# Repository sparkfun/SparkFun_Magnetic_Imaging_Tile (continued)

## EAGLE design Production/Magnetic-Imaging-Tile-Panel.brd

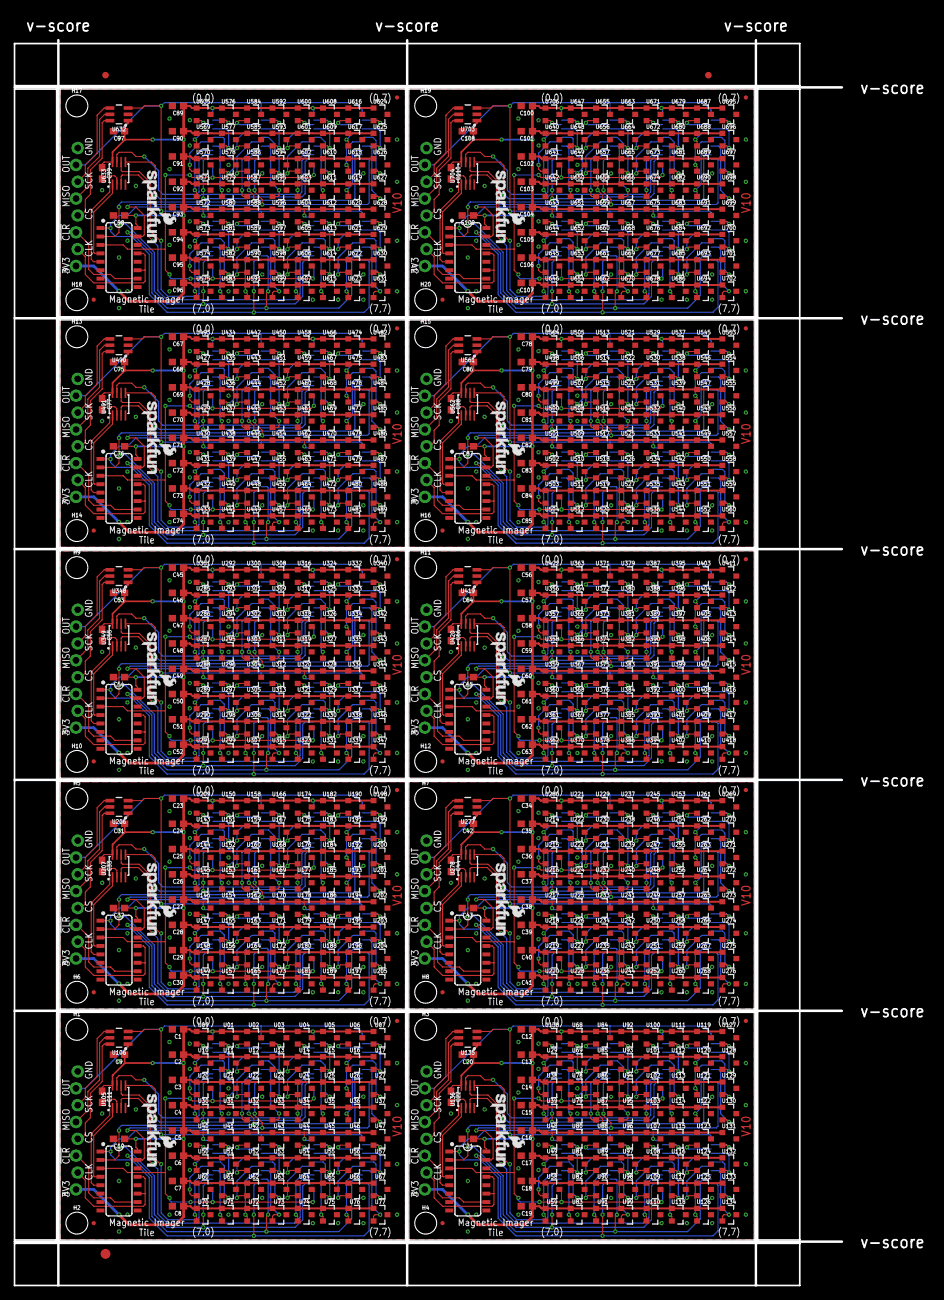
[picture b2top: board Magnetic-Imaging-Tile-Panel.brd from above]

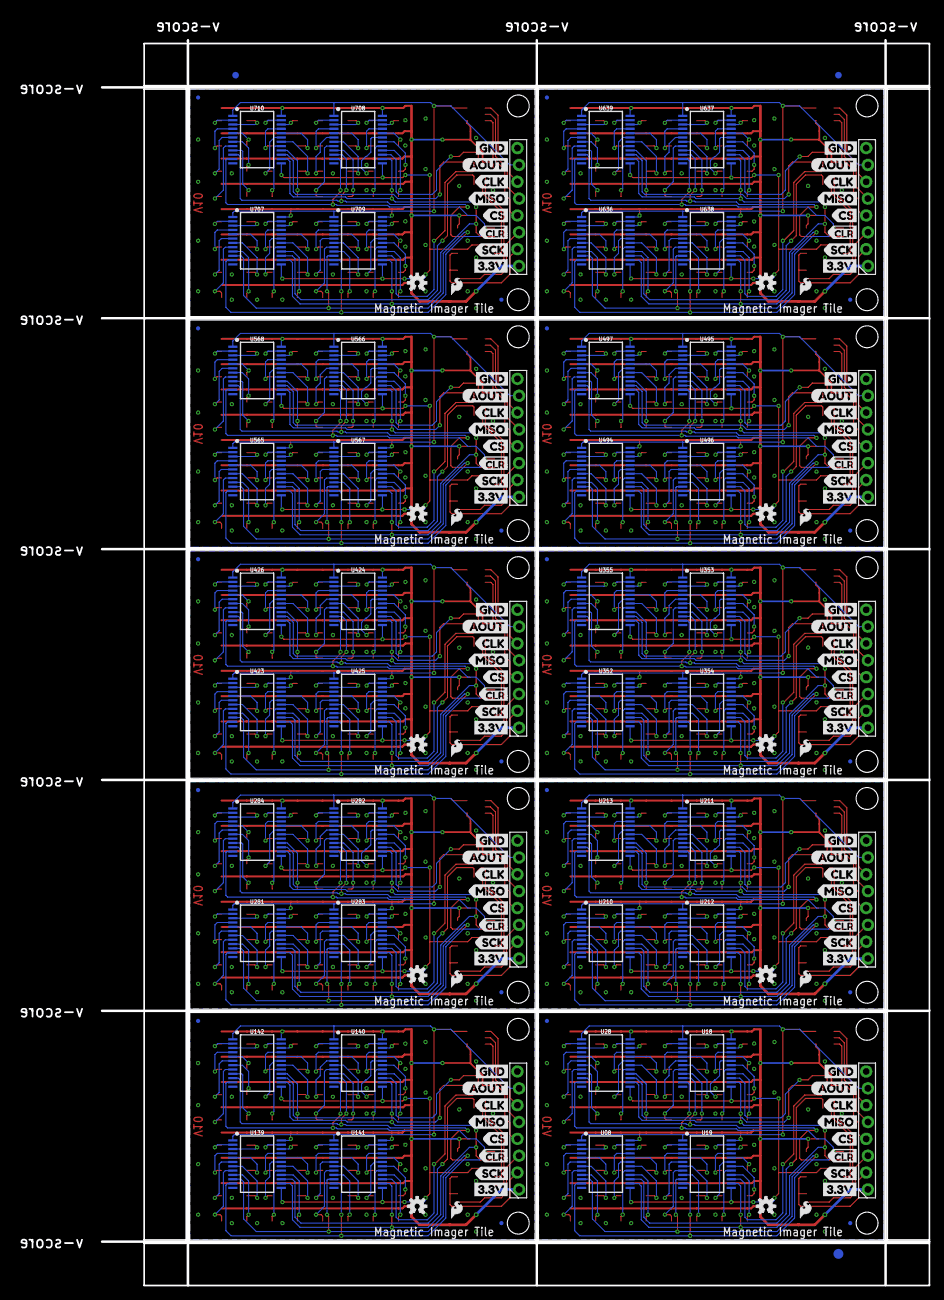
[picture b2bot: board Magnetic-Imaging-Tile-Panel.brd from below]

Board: 2 copper layers, 124.7 x 187.7 mm, 1016 parts (163 on the bottom side), 820 nets.

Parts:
C1, C2, C3, C4, C5, C6, C7, C8, C12, C13, C14, C15, C16, C17, C18, C19, C23, C24, C25, C26, C27, C28, C29, C30, C34, C35, C36, C37, C38, C39, C40, C41, C45, C46, C47, C48, C49, C50, C51, C52, C56, C57, C58, C59, C60, C61, C62, C63, C67, C68, C69, C70, C71, C72, C73, C74, C78, C79, C80, C81, C82, C83, C84, C85, C89, C90, C91, C92, C93, C94, C95, C96, C100, C101, C102, C103, C104, C105, C106, C107: 4.7uF; 0603
C9, C10, C11, C20, C21, C22, C31, C32, C33, C42, C43, C44, C53, C54, C55, C64, C65, C66, C75, C76, C77, C86, C87, C88, C97, C98, C99, C108, C109, C110: 0.1uF; 0603
E$1, E$2, E$3, E$4: FIDUCIAL-1X2
E$5, E$6: FIDUCIAL-1.5X3
FD1, FD2, FD3, FD4, FD5, FD6, FD7, FD8, FD9, FD10, FD11, FD12, FD13, FD14, FD15, FD16, FD17, FD18, FD19, FD20, FD21, FD22, FD23, FD24, FD25, FD26, FD27, FD28, FD29, FD30, FD31, FD32, FD33, FD34, FD35, FD36, FD37, FD38, FD39, FD40: FIDUCIALUFIDUCIAL; FIDUCIAL-MICRO
H1, H2, H3, H4, H5, H6, H7, H8, H9, H10, H11, H12, H13, H14, H15, H16, H17, H18, H19, H20: STAND-OFF
J1, J2, J3, J4, J5, J6, J7, J8, J9, J10: 1X08_LOCK_NO_SILK
LOGO1, LOGO3, LOGO5, LOGO7, LOGO9, LOGO11, LOGO13, LOGO15, LOGO17, LOGO19: SFE_LOGO_NAME.1_INCH; SFE_LOGO_NAME_.1
LOGO2, LOGO4, LOGO6, LOGO8, LOGO10, LOGO12, LOGO14, LOGO16, LOGO18, LOGO20: OSHW-LOGOS; OSHW-LOGO-S
U01, U02, U03, U04, U05, U06, U07, U09, U10, U11, U12, U13, U14, U15, U16, U17, U20, U21, U22, U23, U24, U25, U26, U27, U29, U30, U31, U32, U33, U34, U35, U36, U37, U38, U39, U40, U41, U42, U43, U44, U45, U46, U47, U48, U49, U50, U51, U52, U53, U54, U55, U56, U57, U58, U59, U60, U61, U62, U63, U64, U65, U66, U67, U68, U69, U70, U71, U72, U73, U74, U75, U76, U77, U78, U79, U80, U81, U82, U83, U84, U85, U86, U87, U88, U89, U90, U91, U92, U93, U94, U95, U96, U97, U98, U99, U100, U101, U102, U103, U107, U108, U109, U110, U111, U112, U113, U114, U115, U116, U117, U118, U119, U120, U121, U122, U123, U124, U125, U126, U127, U128, U129, U130, U131, U132, U133, U134, U138, U143, U144, U145, U146, U147, U148, U149, U150, U151, U152, U153, U154, U155, U156, U157, U158, U159, U160, U161, U162, U163, U164, U165, U166, U167, U168, U169, U170, U171, U172, U173, U174, U175, U176, U177, U178, U179, U180, U181, U182, U183, U184, U185, U186, U187, U188, U189, U190, U191, U192, U193, U194, U195, U196, U197, U198, U199, U200, U201, U202, U203, U204, U205, U209, U214, U215, U216, U217, U218, U219, U220, U221, U222, U223, U224, U225, U226, U227, U228, U229, U230, U231, U232, U233, U234, U235, U236, U237, U238, U239, U240, U241, U242, U243, U244, U245, U246, U247, U248, U249, U250, U251, U252, U253, U254, U255, U256, U257, U258, U259, U260, U261, U262, U263, U264, U265, U266, U267, U268, U269, U270, U271, U272, U273, U274, U275, U276, U280, U285, U286, U287, U288, U289, U290, U291, U292, U293, U294, U295, U296, U297, U298, U299, U300, U301, U302, U303, U304, U305, U306, U307, U308, U309, U310, U311, U312, U313, U314, U315, U316, U317, U318, U319, U320, U321, U322, U323, U324, U325, U326, U327, U328, U329, U330, U331, U332, U333, U334, U335, U336, U337, U338, U339, U340, U341, U342, U343, U344, U345, U346, U347, U351, U356, U357, U358, U359, U360, U361, U362, U363, U364, U365, U366, U367, U368, U369, U370, U371, U372, U373, U374, U375, U376, U377, U378, U379, U380, U381, U382, U383, U384, U385, U386, U387, U388, U389, U390, U391, U392, U393, U394, U395, U396, U397, U398, U399, U400, U401, U402, U403, U404, U405, U406, U407, U408, U409, U410, U411, U412, U413, U414, U415, U416, U417, U418, U422, U427, U428, U429, U430, U431, U432, U433, U434, U435, U436, U437, U438, U439, U440, U441, U442, U443, U444, U445, U446, U447, U448, U449, U450, U451, U452, U453, U454, U455, U456, U457, U458, U459, U460, U461, U462, U463, U464, U465, U466, U467, U468, U469, U470, U471, U472, U473, U474, U475, U476, U477, U478, U479, U480, U481, U482, U483, U484, U485, U486, U487, U488, U489, U493, U498, U499, U500, U501, U502, U503, U504, U505, U506, U507, U508, U509, U510, U511, U512, U513, U514, U515, U516, U517, U518, U519, U520, U521, U522, U523, U524, U525, U526, U527, U528, U529, U530, U531, U532, U533, U534, U535, U536, U537, U538, U539, U540, U541, U542, U543, U544, U545, U546, U547, U548, U549, U550, U551, U552, U553, U554, U555, U556, U557, U558, U559, U560, U564, U569, U570, U571, U572, U573, U574, U575, U576, U577, U578, U579, U580, U581, U582, U583, U584, U585, U586, U587, U588, U589, U590, U591, U592, U593, U594, U595, U596, U597, U598, U599, U600, U601, U602, U603, U604, U605, U606, U607, U608, U609, U610, U611, U612, U613, U614, U615, U616, U617, U618, U619, U620, U621, U622, U623, U624, U625, U626, U627, U628, U629, U630, U631, U635, U640, U641, U642, U643, U644, U645, U646, U647, U648, U649, U650, U651, U652, U653, U654, U655, U656, U657, U658, U659, U660, U661, U662, U663, U664, U665, U666, U667, U668, U669, U670, U671, U672, U673, U674, U675, U676, U677, U678, U679, U680, U681, U682, U683, U684, U685, U686, U687, U688, U689, U690, U691, U692, U693, U694, U695, U696, U697, U698, U699, U700, U701, U702, U706: DRV5053; SOT23-3
U08, U18, U19, U28, U139, U140, U141, U142, U210, U211, U212, U213, U281, U282, U283, U284, U352, U353, U354, U355, U423, U424, U425, U426, U494, U495, U496, U497, U565, U566, U567, U568, U636, U637, U638, U639, U707, U708, U709, U710: CD74HC4067; SSOP24
U104, U137, U208, U279, U350, U421, U492, U563, U634, U705: SN74HC590A; SO16
U105, U136, U207, U278, U349, U420, U491, U562, U633, U704: SN74LVC1G139; SM8
U106, U135, U206, U277, U348, U419, U490, U561, U632, U703: AD7680; SOT23-6
U$1, U$2, U$19, U$20, U$29, U$30, U$39, U$40, U$49, U$50, U$59, U$60, U$69, U$70, U$79, U$80, U$89, U$90, U$99, U$100: SFE_LOGO_FLAME_.1
U$3, U$11, U$21, U$31, U$41, U$51, U$61, U$71, U$81, U$91: GND
U$4, U$17, U$27, U$37, U$47, U$57, U$67, U$77, U$87, U$97: #CLR
U$5, U$12, U$22, U$32, U$42, U$52, U$62, U$72, U$82, U$92: 3#3V
U$6, U$13, U$23, U$33, U$43, U$53, U$63, U$73, U$83, U$93: AOUT
U$7, U$14, U$24, U$34, U$44, U$54, U$64, U$74, U$84, U$94: CLK
U$8, U$15, U$25, U$35, U$45, U$55, U$65, U$75, U$85, U$95: MISO
U$9, U$16, U$26, U$36, U$46, U$56, U$66, U$76, U$86, U$96: SCK
U$10, U$18, U$28, U$38, U$48, U$58, U$68, U$78, U$88, U$98: CS

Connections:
1I0: U18.9, U32.2
1I1: U18.8, U33.2
1I2: U18.7, U22.2
1I3: U18.6, U23.2
1I4: U12.2, U18.5
1I5: U13.2, U18.4
1I6: U02.2, U18.3
1I7: U03.2, U18.2
1I8: U01.2, U18.23
1I9: U09.2, U18.22
1I10: U11.2, U18.21
1I11: U10.2, U18.20
1I12: U18.19, U21.2
1I13: U18.18, U20.2
1I14: U18.17, U31.2
1I15: U18.16, U30.2
1I16: U87.2, U140.9
1I17: U95.2, U140.8
1I18: U86.2, U140.7
1I19: U94.2, U140.6
1I20: U85.2, U140.5
1I21: U93.2, U140.4
1I22: U84.2, U140.3
1I23: U92.2, U140.2
1I24: U68.2, U140.23
1I25: U138.2, U140.22
1I26: U69.2, U140.21
1I27: U29.2, U140.20
1I28: U78.2, U140.19
1I29: U38.2, U140.18
1I30: U79.2, U140.17
1I31: U39.2, U140.16
1I32: U161.2, U211.9
1I33: U169.2, U211.8
1I34: U160.2, U211.7
1I35: U168.2, U211.6
1I36: U159.2, U211.5
1I37: U167.2, U211.4
1I38: U158.2, U211.3
1I39: U166.2, U211.2
1I40: U150.2, U211.23
1I41: U209.2, U211.22
1I42: U151.2, U211.21
1I43: U143.2, U211.20
1I44: U152.2, U211.19
1I45: U144.2, U211.18
1I46: U153.2, U211.17
1I47: U145.2, U211.16
1I48: U232.2, U282.9
1I49: U240.2, U282.8
1I50: U231.2, U282.7
1I51: U239.2, U282.6
1I52: U230.2, U282.5
1I53: U238.2, U282.4
1I54: U229.2, U282.3
1I55: U237.2, U282.2
1I56: U221.2, U282.23
1I57: U280.2, U282.22
1I58: U222.2, U282.21
1I59: U214.2, U282.20
1I60: U223.2, U282.19
1I61: U215.2, U282.18
1I62: U224.2, U282.17
1I63: U216.2, U282.16
1I64: U303.2, U353.9
1I65: U311.2, U353.8
1I66: U302.2, U353.7
1I67: U310.2, U353.6
1I68: U301.2, U353.5
1I69: U309.2, U353.4
1I70: U300.2, U353.3
1I71: U308.2, U353.2
1I72: U292.2, U353.23
1I73: U351.2, U353.22
1I74: U293.2, U353.21
1I75: U285.2, U353.20
1I76: U294.2, U353.19
1I77: U286.2, U353.18
1I78: U295.2, U353.17
1I79: U287.2, U353.16
1I80: U374.2, U424.9
1I81: U382.2, U424.8
1I82: U373.2, U424.7
1I83: U381.2, U424.6
1I84: U372.2, U424.5
1I85: U380.2, U424.4
1I86: U371.2, U424.3
1I87: U379.2, U424.2
1I88: U363.2, U424.23
1I89: U422.2, U424.22
1I90: U364.2, U424.21
1I91: U356.2, U424.20
1I92: U365.2, U424.19
1I93: U357.2, U424.18
1I94: U366.2, U424.17
1I95: U358.2, U424.16
1I96: U445.2, U495.9
1I97: U453.2, U495.8
1I98: U444.2, U495.7
1I99: U452.2, U495.6
1I100: U443.2, U495.5
1I101: U451.2, U495.4
1I102: U442.2, U495.3
1I103: U450.2, U495.2
1I104: U434.2, U495.23
1I105: U493.2, U495.22
1I106: U435.2, U495.21
1I107: U427.2, U495.20
1I108: U436.2, U495.19
1I109: U428.2, U495.18
1I110: U437.2, U495.17
1I111: U429.2, U495.16
1I112: U516.2, U566.9
1I113: U524.2, U566.8
1I114: U515.2, U566.7
1I115: U523.2, U566.6
1I116: U514.2, U566.5
1I117: U522.2, U566.4
1I118: U513.2, U566.3
1I119: U521.2, U566.2
1I120: U505.2, U566.23
1I121: U564.2, U566.22
1I122: U506.2, U566.21
1I123: U498.2, U566.20
1I124: U507.2, U566.19
1I125: U499.2, U566.18
1I126: U508.2, U566.17
1I127: U500.2, U566.16
1I128: U587.2, U637.9
1I129: U595.2, U637.8
1I130: U586.2, U637.7
1I131: U594.2, U637.6
1I132: U585.2, U637.5
1I133: U593.2, U637.4
1I134: U584.2, U637.3
1I135: U592.2, U637.2
1I136: U576.2, U637.23
1I137: U635.2, U637.22
1I138: U577.2, U637.21
1I139: U569.2, U637.20
1I140: U578.2, U637.19
1I141: U570.2, U637.18
1I142: U579.2, U637.17
1I143: U571.2, U637.16
1I144: U658.2, U708.9
1I145: U666.2, U708.8
1I146: U657.2, U708.7
1I147: U665.2, U708.6
1I148: U656.2, U708.5
1I149: U664.2, U708.4
1I150: U655.2, U708.3
1I151: U663.2, U708.2
1I152: U647.2, U708.23
1I153: U706.2, U708.22
1I154: U648.2, U708.21
1I155: U640.2, U708.20
1I156: U649.2, U708.19
1I157: U641.2, U708.18
1I158: U650.2, U708.17
1I159: U642.2, U708.16
2I0: U19.9, U72.2
2I1: U19.8, U73.2
2I2: U19.7, U62.2
2I3: U19.6, U63.2
2I4: U19.5, U52.2
2I5: U19.4, U53.2
2I6: U19.3, U42.2
2I7: U19.2, U43.2
2I8: U19.23, U41.2
2I9: U19.22, U40.2
2I10: U19.21, U51.2
2I11: U19.20, U50.2
2I12: U19.19, U61.2
2I13: U19.18, U60.2
2I14: U19.17, U71.2
2I15: U19.16, U70.2
2I16: U91.2, U141.9
2I17: U99.2, U141.8
2I18: U90.2, U141.7
2I19: U98.2, U141.6
2I20: U89.2, U141.5
2I21: U97.2, U141.4
2I22: U88.2, U141.3
2I23: U96.2, U141.2
2I24: U80.2, U141.23
2I25: U48.2, U141.22
2I26: U81.2, U141.21
2I27: U49.2, U141.20
2I28: U82.2, U141.19
2I29: U58.2, U141.18
2I30: U83.2, U141.17
2I31: U59.2, U141.16
2I32: U165.2, U212.9
2I33: U173.2, U212.8
2I34: U164.2, U212.7
2I35: U172.2, U212.6
2I36: U163.2, U212.5
2I37: U171.2, U212.4
2I38: U162.2, U212.3
2I39: U170.2, U212.2
2I40: U154.2, U212.23
2I41: U146.2, U212.22
2I42: U155.2, U212.21
2I43: U147.2, U212.20
2I44: U156.2, U212.19
2I45: U148.2, U212.18
2I46: U157.2, U212.17
2I47: U149.2, U212.16
2I48: U236.2, U283.9
2I49: U244.2, U283.8
2I50: U235.2, U283.7
2I51: U243.2, U283.6
2I52: U234.2, U283.5
2I53: U242.2, U283.4
2I54: U233.2, U283.3
2I55: U241.2, U283.2
2I56: U225.2, U283.23
2I57: U217.2, U283.22
2I58: U226.2, U283.21
2I59: U218.2, U283.20
2I60: U227.2, U283.19
2I61: U219.2, U283.18
2I62: U228.2, U283.17
2I63: U220.2, U283.16
2I64: U307.2, U354.9
2I65: U315.2, U354.8
2I66: U306.2, U354.7
2I67: U314.2, U354.6
2I68: U305.2, U354.5
2I69: U313.2, U354.4
2I70: U304.2, U354.3
2I71: U312.2, U354.2
2I72: U296.2, U354.23
2I73: U288.2, U354.22
2I74: U297.2, U354.21
2I75: U289.2, U354.20
2I76: U298.2, U354.19
2I77: U290.2, U354.18
2I78: U299.2, U354.17
2I79: U291.2, U354.16
2I80: U378.2, U425.9
2I81: U386.2, U425.8
2I82: U377.2, U425.7
2I83: U385.2, U425.6
2I84: U376.2, U425.5
2I85: U384.2, U425.4
2I86: U375.2, U425.3
2I87: U383.2, U425.2
2I88: U367.2, U425.23
2I89: U359.2, U425.22
2I90: U368.2, U425.21
2I91: U360.2, U425.20
2I92: U369.2, U425.19
2I93: U361.2, U425.18
2I94: U370.2, U425.17
2I95: U362.2, U425.16
2I96: U449.2, U496.9
2I97: U457.2, U496.8
2I98: U448.2, U496.7
2I99: U456.2, U496.6
2I100: U447.2, U496.5
2I101: U455.2, U496.4
2I102: U446.2, U496.3
2I103: U454.2, U496.2
2I104: U438.2, U496.23
2I105: U430.2, U496.22
2I106: U439.2, U496.21
2I107: U431.2, U496.20
2I108: U440.2, U496.19
2I109: U432.2, U496.18
2I110: U441.2, U496.17
2I111: U433.2, U496.16
2I112: U520.2, U567.9
2I113: U528.2, U567.8
2I114: U519.2, U567.7
2I115: U527.2, U567.6
2I116: U518.2, U567.5
2I117: U526.2, U567.4
2I118: U517.2, U567.3
2I119: U525.2, U567.2
2I120: U509.2, U567.23
2I121: U501.2, U567.22
2I122: U510.2, U567.21
2I123: U502.2, U567.20
2I124: U511.2, U567.19
2I125: U503.2, U567.18
2I126: U512.2, U567.17
2I127: U504.2, U567.16
2I128: U591.2, U638.9
2I129: U599.2, U638.8
2I130: U590.2, U638.7
2I131: U598.2, U638.6
2I132: U589.2, U638.5
2I133: U597.2, U638.4
2I134: U588.2, U638.3
2I135: U596.2, U638.2
2I136: U580.2, U638.23
2I137: U572.2, U638.22
2I138: U581.2, U638.21
2I139: U573.2, U638.20
2I140: U582.2, U638.19
2I141: U574.2, U638.18
2I142: U583.2, U638.17
2I143: U575.2, U638.16
2I144: U662.2, U709.9
2I145: U670.2, U709.8
2I146: U661.2, U709.7
2I147: U669.2, U709.6
2I148: U660.2, U709.5
2I149: U668.2, U709.4
2I150: U659.2, U709.3
2I151: U667.2, U709.2
2I152: U651.2, U709.23
2I153: U643.2, U709.22
2I154: U652.2, U709.21
2I155: U644.2, U709.20
2I156: U653.2, U709.19
2I157: U645.2, U709.18
2I158: U654.2, U709.17
2I159: U646.2, U709.16
3.3V: C1.1, C2.1, C3.1, C4.1, C5.1, C6.1, C7.1, C8.1, C9.1, C10.1, C11.1, J1.1, U01.1, U02.1, U03.1, U04.1, U05.1, U06.1, U07.1, U08.24, U09.1, U10.1, U11.1, U12.1, U13.1, U14.1, U15.1, U16.1, U17.1, U18.24, U19.24, U20.1, U21.1, U22.1, U23.1, U24.1, U25.1, U26.1, U27.1, U28.24, U30.1, U31.1, U32.1, U33.1, U34.1, U35.1, U36.1, U37.1, U40.1, U41.1, U42.1, U43.1, U44.1, U45.1, U46.1, U47.1, U50.1, U51.1, U52.1, U53.1, U54.1, U55.1, U56.1, U57.1, U60.1, U61.1, U62.1, U63.1, U64.1, U65.1, U66.1, U67.1, U70.1, U71.1, U72.1, U73.1, U74.1, U75.1, U76.1, U77.1, U104.16, U105.8, U106.1
3.3V1: C12.1, C13.1, C14.1, C15.1, C16.1, C17.1, C18.1, C19.1, C20.1, C21.1, C22.1, J2.1, U29.1, U38.1, U39.1, U48.1, U49.1, U58.1, U59.1, U68.1, U69.1, U78.1, U79.1, U80.1, U81.1, U82.1, U83.1, U84.1, U85.1, U86.1, U87.1, U88.1, U89.1, U90.1, U91.1, U92.1, U93.1, U94.1, U95.1, U96.1, U97.1, U98.1, U99.1, U100.1, U101.1, U102.1, U103.1, U107.1, U108.1, U109.1, U110.1, U111.1, U112.1, U113.1, U114.1, U115.1, U116.1, U117.1, U118.1, U119.1, U120.1, U121.1, U122.1, U123.1, U124.1, U125.1, U126.1, U127.1, U128.1, U129.1, U130.1, U131.1, U132.1, U133.1, U134.1, U135.1, U136.8, U137.16, U138.1, U139.24, U140.24, U141.24, U142.24
3.3V2: C23.1, C24.1, C25.1, C26.1, C27.1, C28.1, C29.1, C30.1, C31.1, C32.1, C33.1, J3.1, U143.1, U144.1, U145.1, U146.1, U147.1, U148.1, U149.1, U150.1, U151.1, U152.1, U153.1, U154.1, U155.1, U156.1, U157.1, U158.1, U159.1, U160.1, U161.1, U162.1, U163.1, U164.1, U165.1, U166.1, U167.1, U168.1, U169.1, U170.1, U171.1, U172.1, U173.1, U174.1, U175.1, U176.1, U177.1, U178.1, U179.1, U180.1, U181.1, U182.1, U183.1, U184.1, U185.1, U186.1, U187.1, U188.1, U189.1, U190.1, U191.1, U192.1, U193.1, U194.1, U195.1, U196.1, U197.1, U198.1, U199.1, U200.1, U201.1, U202.1, U203.1, U204.1, U205.1, U206.1, U207.8, U208.16, U209.1, U210.24, U211.24, U212.24, U213.24
3.3V3: C34.1, C35.1, C36.1, C37.1, C38.1, C39.1, C40.1, C41.1, C42.1, C43.1, C44.1, J4.1, U214.1, U215.1, U216.1, U217.1, U218.1, U219.1, U220.1, U221.1, U222.1, U223.1, U224.1, U225.1, U226.1, U227.1, U228.1, U229.1, U230.1, U231.1, U232.1, U233.1, U234.1, U235.1, U236.1, U237.1, U238.1, U239.1, U240.1, U241.1, U242.1, U243.1, U244.1, U245.1, U246.1, U247.1, U248.1, U249.1, U250.1, U251.1, U252.1, U253.1, U254.1, U255.1, U256.1, U257.1, U258.1, U259.1, U260.1, U261.1, U262.1, U263.1, U264.1, U265.1, U266.1, U267.1, U268.1, U269.1, U270.1, U271.1, U272.1, U273.1, U274.1, U275.1, U276.1, U277.1, U278.8, U279.16, U280.1, U281.24, U282.24, U283.24, U284.24
3.3V4: C45.1, C46.1, C47.1, C48.1, C49.1, C50.1, C51.1, C52.1, C53.1, C54.1, C55.1, J5.1, U285.1, U286.1, U287.1, U288.1, U289.1, U290.1, U291.1, U292.1, U293.1, U294.1, U295.1, U296.1, U297.1, U298.1, U299.1, U300.1, U301.1, U302.1, U303.1, U304.1, U305.1, U306.1, U307.1, U308.1, U309.1, U310.1, U311.1, U312.1, U313.1, U314.1, U315.1, U316.1, U317.1, U318.1, U319.1, U320.1, U321.1, U322.1, U323.1, U324.1, U325.1, U326.1, U327.1, U328.1, U329.1, U330.1, U331.1, U332.1, U333.1, U334.1, U335.1, U336.1, U337.1, U338.1, U339.1, U340.1, U341.1, U342.1, U343.1, U344.1, U345.1, U346.1, U347.1, U348.1, U349.8, U350.16, U351.1, U352.24, U353.24, U354.24, U355.24
3.3V5: C56.1, C57.1, C58.1, C59.1, C60.1, C61.1, C62.1, C63.1, C64.1, C65.1, C66.1, J6.1, U356.1, U357.1, U358.1, U359.1, U360.1, U361.1, U362.1, U363.1, U364.1, U365.1, U366.1, U367.1, U368.1, U369.1, U370.1, U371.1, U372.1, U373.1, U374.1, U375.1, U376.1, U377.1, U378.1, U379.1, U380.1, U381.1, U382.1, U383.1, U384.1, U385.1, U386.1, U387.1, U388.1, U389.1, U390.1, U391.1, U392.1, U393.1, U394.1, U395.1, U396.1, U397.1, U398.1, U399.1, U400.1, U401.1, U402.1, U403.1, U404.1, U405.1, U406.1, U407.1, U408.1, U409.1, U410.1, U411.1, U412.1, U413.1, U414.1, U415.1, U416.1, U417.1, U418.1, U419.1, U420.8, U421.16, U422.1, U423.24, U424.24, U425.24, U426.24
3.3V6: C67.1, C68.1, C69.1, C70.1, C71.1, C72.1, C73.1, C74.1, C75.1, C76.1, C77.1, J7.1, U427.1, U428.1, U429.1, U430.1, U431.1, U432.1, U433.1, U434.1, U435.1, U436.1, U437.1, U438.1, U439.1, U440.1, U441.1, U442.1, U443.1, U444.1, U445.1, U446.1, U447.1, U448.1, U449.1, U450.1, U451.1, U452.1, U453.1, U454.1, U455.1, U456.1, U457.1, U458.1, U459.1, U460.1, U461.1, U462.1, U463.1, U464.1, U465.1, U466.1, U467.1, U468.1, U469.1, U470.1, U471.1, U472.1, U473.1, U474.1, U475.1, U476.1, U477.1, U478.1, U479.1, U480.1, U481.1, U482.1, U483.1, U484.1, U485.1, U486.1, U487.1, U488.1, U489.1, U490.1, U491.8, U492.16, U493.1, U494.24, U495.24, U496.24, U497.24
3.3V7: C78.1, C79.1, C80.1, C81.1, C82.1, C83.1, C84.1, C85.1, C86.1, C87.1, C88.1, J8.1, U498.1, U499.1, U500.1, U501.1, U502.1, U503.1, U504.1, U505.1, U506.1, U507.1, U508.1, U509.1, U510.1, U511.1, U512.1, U513.1, U514.1, U515.1, U516.1, U517.1, U518.1, U519.1, U520.1, U521.1, U522.1, U523.1, U524.1, U525.1, U526.1, U527.1, U528.1, U529.1, U530.1, U531.1, U532.1, U533.1, U534.1, U535.1, U536.1, U537.1, U538.1, U539.1, U540.1, U541.1, U542.1, U543.1, U544.1, U545.1, U546.1, U547.1, U548.1, U549.1, U550.1, U551.1, U552.1, U553.1, U554.1, U555.1, U556.1, U557.1, U558.1, U559.1, U560.1, U561.1, U562.8, U563.16, U564.1, U565.24, U566.24, U567.24, U568.24
3.3V8: C89.1, C90.1, C91.1, C92.1, C93.1, C94.1, C95.1, C96.1, C97.1, C98.1, C99.1, J9.1, U569.1, U570.1, U571.1, U572.1, U573.1, U574.1, U575.1, U576.1, U577.1, U578.1, U579.1, U580.1, U581.1, U582.1, U583.1, U584.1, U585.1, U586.1, U587.1, U588.1, U589.1, U590.1, U591.1, U592.1, U593.1, U594.1, U595.1, U596.1, U597.1, U598.1, U599.1, U600.1, U601.1, U602.1, U603.1, U604.1, U605.1, U606.1, U607.1, U608.1, U609.1, U610.1, U611.1, U612.1, U613.1, U614.1, U615.1, U616.1, U617.1, U618.1, U619.1, U620.1, U621.1, U622.1, U623.1, U624.1, U625.1, U626.1, U627.1, U628.1, U629.1, U630.1, U631.1, U632.1, U633.8, U634.16, U635.1, U636.24, U637.24, U638.24, U639.24
3.3V9: C100.1, C101.1, C102.1, C103.1, C104.1, C105.1, C106.1, C107.1, C108.1, C109.1, C110.1, J10.1, U640.1, U641.1, U642.1, U643.1, U644.1, U645.1, U646.1, U647.1, U648.1, U649.1, U650.1, U651.1, U652.1, U653.1, U654.1, U655.1, U656.1, U657.1, U658.1, U659.1, U660.1, U661.1, U662.1, U663.1, U664.1, U665.1, U666.1, U667.1, U668.1, U669.1, U670.1, U671.1, U672.1, U673.1, U674.1, U675.1, U676.1, U677.1, U678.1, U679.1, U680.1, U681.1, U682.1, U683.1, U684.1, U685.1, U686.1, U687.1, U688.1, U689.1, U690.1, U691.1, U692.1, U693.1, U694.1, U695.1, U696.1, U697.1, U698.1, U699.1, U700.1, U701.1, U702.1, U703.1, U704.8, U705.16, U706.1, U707.24, U708.24, U709.24, U710.24
3I0: U28.9, U36.2
3I1: U28.8, U37.2
3I2: U26.2, U28.7
3I3: U27.2, U28.6
3I4: U16.2, U28.5
3I5: U17.2, U28.4
3I6: U06.2, U28.3
3I7: U07.2, U28.2
3I8: U05.2, U28.23
3I9: U04.2, U28.22
3I10: U15.2, U28.21
3I11: U14.2, U28.20
3I12: U25.2, U28.19
3I13: U24.2, U28.18
3I14: U28.17, U35.2
3I15: U28.16, U34.2
3I16: U122.2, U142.9
3I17: U130.2, U142.8
3I18: U121.2, U142.7
3I19: U129.2, U142.6
3I20: U120.2, U142.5
3I21: U128.2, U142.4
3I22: U119.2, U142.3
3I23: U127.2, U142.2
3I24: U111.2, U142.23
3I25: U100.2, U142.22
3I26: U112.2, U142.21
3I27: U101.2, U142.20
3I28: U113.2, U142.19
3I29: U102.2, U142.18
3I30: U114.2, U142.17
3I31: U103.2, U142.16
3I32: U193.2, U213.9
3I33: U201.2, U213.8
3I34: U192.2, U213.7
3I35: U200.2, U213.6
3I36: U191.2, U213.5
3I37: U199.2, U213.4
3I38: U190.2, U213.3
3I39: U198.2, U213.2
3I40: U182.2, U213.23
3I41: U174.2, U213.22
3I42: U183.2, U213.21
3I43: U175.2, U213.20
3I44: U184.2, U213.19
3I45: U176.2, U213.18
3I46: U185.2, U213.17
3I47: U177.2, U213.16
3I48: U264.2, U284.9
3I49: U272.2, U284.8
3I50: U263.2, U284.7
3I51: U271.2, U284.6
3I52: U262.2, U284.5
3I53: U270.2, U284.4
3I54: U261.2, U284.3
3I55: U269.2, U284.2
3I56: U253.2, U284.23
3I57: U245.2, U284.22
3I58: U254.2, U284.21
3I59: U246.2, U284.20
3I60: U255.2, U284.19
3I61: U247.2, U284.18
3I62: U256.2, U284.17
3I63: U248.2, U284.16
3I64: U335.2, U355.9
3I65: U343.2, U355.8
3I66: U334.2, U355.7
3I67: U342.2, U355.6
3I68: U333.2, U355.5
3I69: U341.2, U355.4
3I70: U332.2, U355.3
3I71: U340.2, U355.2
3I72: U324.2, U355.23
3I73: U316.2, U355.22
3I74: U325.2, U355.21
3I75: U317.2, U355.20
3I76: U326.2, U355.19
3I77: U318.2, U355.18
3I78: U327.2, U355.17
3I79: U319.2, U355.16
3I80: U406.2, U426.9
3I81: U414.2, U426.8
3I82: U405.2, U426.7
3I83: U413.2, U426.6
3I84: U404.2, U426.5
3I85: U412.2, U426.4
3I86: U403.2, U426.3
3I87: U411.2, U426.2
3I88: U395.2, U426.23
3I89: U387.2, U426.22
3I90: U396.2, U426.21
3I91: U388.2, U426.20
3I92: U397.2, U426.19
3I93: U389.2, U426.18
3I94: U398.2, U426.17
3I95: U390.2, U426.16
3I96: U477.2, U497.9
3I97: U485.2, U497.8
3I98: U476.2, U497.7
3I99: U484.2, U497.6
3I100: U475.2, U497.5
3I101: U483.2, U497.4
3I102: U474.2, U497.3
3I103: U482.2, U497.2
3I104: U466.2, U497.23
3I105: U458.2, U497.22
3I106: U467.2, U497.21
3I107: U459.2, U497.20
3I108: U468.2, U497.19
3I109: U460.2, U497.18
3I110: U469.2, U497.17
3I111: U461.2, U497.16
3I112: U548.2, U568.9
3I113: U556.2, U568.8
3I114: U547.2, U568.7
3I115: U555.2, U568.6
3I116: U546.2, U568.5
3I117: U554.2, U568.4
3I118: U545.2, U568.3
3I119: U553.2, U568.2
3I120: U537.2, U568.23
3I121: U529.2, U568.22
3I122: U538.2, U568.21
3I123: U530.2, U568.20
3I124: U539.2, U568.19
3I125: U531.2, U568.18
3I126: U540.2, U568.17
3I127: U532.2, U568.16
3I128: U619.2, U639.9
3I129: U627.2, U639.8
3I130: U618.2, U639.7
3I131: U626.2, U639.6
3I132: U617.2, U639.5
3I133: U625.2, U639.4
3I134: U616.2, U639.3
3I135: U624.2, U639.2
3I136: U608.2, U639.23
3I137: U600.2, U639.22
3I138: U609.2, U639.21
3I139: U601.2, U639.20
3I140: U610.2, U639.19
3I141: U602.2, U639.18
3I142: U611.2, U639.17
3I143: U603.2, U639.16
3I144: U690.2, U710.9
3I145: U698.2, U710.8
3I146: U689.2, U710.7
3I147: U697.2, U710.6
3I148: U688.2, U710.5
3I149: U696.2, U710.4
3I150: U687.2, U710.3
3I151: U695.2, U710.2
3I152: U679.2, U710.23
3I153: U671.2, U710.22
3I154: U680.2, U710.21
3I155: U672.2, U710.20
3I156: U681.2, U710.19
3I157: U673.2, U710.18
3I158: U682.2, U710.17
3I159: U674.2, U710.16
4I0: U08.9, U76.2
4I1: U08.8, U77.2
4I2: U08.7, U66.2
4I3: U08.6, U67.2
4I4: U08.5, U56.2
4I5: U08.4, U57.2
4I6: U08.3, U46.2
4I7: U08.2, U47.2
4I8: U08.23, U45.2
4I9: U08.22, U44.2
4I10: U08.21, U55.2
4I11: U08.20, U54.2
4I12: U08.19, U65.2
4I13: U08.18, U64.2
4I14: U08.17, U75.2
4I15: U08.16, U74.2
4I16: U126.2, U139.9
4I17: U134.2, U139.8
4I18: U125.2, U139.7
4I19: U133.2, U139.6
4I20: U124.2, U139.5
4I21: U132.2, U139.4
4I22: U123.2, U139.3
4I23: U131.2, U139.2
4I24: U115.2, U139.23
4I25: U107.2, U139.22
4I26: U116.2, U139.21
4I27: U108.2, U139.20
4I28: U117.2, U139.19
4I29: U109.2, U139.18
4I30: U118.2, U139.17
4I31: U110.2, U139.16
4I32: U197.2, U210.9
4I33: U205.2, U210.8
4I34: U196.2, U210.7
4I35: U204.2, U210.6
4I36: U195.2, U210.5
4I37: U203.2, U210.4
4I38: U194.2, U210.3
4I39: U202.2, U210.2
4I40: U186.2, U210.23
4I41: U178.2, U210.22
4I42: U187.2, U210.21
4I43: U179.2, U210.20
4I44: U188.2, U210.19
4I45: U180.2, U210.18
4I46: U189.2, U210.17
4I47: U181.2, U210.16
4I48: U268.2, U281.9
4I49: U276.2, U281.8
4I50: U267.2, U281.7
4I51: U275.2, U281.6
4I52: U266.2, U281.5
4I53: U274.2, U281.4
4I54: U265.2, U281.3
4I55: U273.2, U281.2
4I56: U257.2, U281.23
4I57: U249.2, U281.22
4I58: U258.2, U281.21
4I59: U250.2, U281.20
4I60: U259.2, U281.19
4I61: U251.2, U281.18
4I62: U260.2, U281.17
4I63: U252.2, U281.16
4I64: U339.2, U352.9
4I65: U347.2, U352.8
4I66: U338.2, U352.7
4I67: U346.2, U352.6
4I68: U337.2, U352.5
4I69: U345.2, U352.4
4I70: U336.2, U352.3
4I71: U344.2, U352.2
4I72: U328.2, U352.23
4I73: U320.2, U352.22
4I74: U329.2, U352.21
4I75: U321.2, U352.20
4I76: U330.2, U352.19
4I77: U322.2, U352.18
4I78: U331.2, U352.17
4I79: U323.2, U352.16
4I80: U410.2, U423.9
4I81: U418.2, U423.8
4I82: U409.2, U423.7
4I83: U417.2, U423.6
4I84: U408.2, U423.5
4I85: U416.2, U423.4
4I86: U407.2, U423.3
4I87: U415.2, U423.2
4I88: U399.2, U423.23
4I89: U391.2, U423.22
4I90: U400.2, U423.21
4I91: U392.2, U423.20
4I92: U401.2, U423.19
4I93: U393.2, U423.18
4I94: U402.2, U423.17
4I95: U394.2, U423.16
4I96: U481.2, U494.9
4I97: U489.2, U494.8
4I98: U480.2, U494.7
4I99: U488.2, U494.6
4I100: U479.2, U494.5
4I101: U487.2, U494.4
4I102: U478.2, U494.3
4I103: U486.2, U494.2
4I104: U470.2, U494.23
4I105: U462.2, U494.22
4I106: U471.2, U494.21
4I107: U463.2, U494.20
4I108: U472.2, U494.19
4I109: U464.2, U494.18
4I110: U473.2, U494.17
4I111: U465.2, U494.16
4I112: U552.2, U565.9
4I113: U560.2, U565.8
4I114: U551.2, U565.7
4I115: U559.2, U565.6
4I116: U550.2, U565.5
4I117: U558.2, U565.4
4I118: U549.2, U565.3
4I119: U557.2, U565.2
4I120: U541.2, U565.23
4I121: U533.2, U565.22
4I122: U542.2, U565.21
4I123: U534.2, U565.20
4I124: U543.2, U565.19
4I125: U535.2, U565.18
4I126: U544.2, U565.17
4I127: U536.2, U565.16
4I128: U623.2, U636.9
4I129: U631.2, U636.8
4I130: U622.2, U636.7
4I131: U630.2, U636.6
4I132: U621.2, U636.5
4I133: U629.2, U636.4
4I134: U620.2, U636.3
4I135: U628.2, U636.2
4I136: U612.2, U636.23
4I137: U604.2, U636.22
4I138: U613.2, U636.21
4I139: U605.2, U636.20
4I140: U614.2, U636.19
4I141: U606.2, U636.18
4I142: U615.2, U636.17
4I143: U607.2, U636.16
4I144: U694.2, U707.9
4I145: U702.2, U707.8
4I146: U693.2, U707.7
4I147: U701.2, U707.6
4I148: U692.2, U707.5
4I149: U700.2, U707.4
4I150: U691.2, U707.3
4I151: U699.2, U707.2
4I152: U683.2, U707.23
4I153: U675.2, U707.22
4I154: U684.2, U707.21
4I155: U676.2, U707.20
4I156: U685.2, U707.19
4I157: U677.2, U707.18
4I158: U686.2, U707.17
4I159: U678.2, U707.16
!CCLR: J1.3, U104.10
!CCLR1: J2.3, U137.10
!CCLR2: J3.3, U208.10
!CCLR3: J4.3, U279.10
!CCLR4: J5.3, U350.10
!CCLR5: J6.3, U421.10
!CCLR6: J7.3, U492.10
!CCLR7: J8.3, U563.10
!CCLR8: J9.3, U634.10
!CCLR9: J10.3, U705.10
!EN1: U18.15, U105.7
!EN2: U19.15, U105.6
!EN3: U28.15, U105.5
!EN4: U08.15, U105.3
!EN5: U136.3, U139.15
!EN6: U136.7, U140.15
!EN7: U136.6, U141.15
!EN8: U136.5, U142.15
!EN9: U207.3, U210.15
!EN10: U207.7, U211.15
!EN11: U207.6, U212.15
!EN12: U207.5, U213.15
!EN13: U278.3, U281.15
!EN14: U278.7, U282.15
!EN15: U278.6, U283.15
!EN16: U278.5, U284.15
!EN17: U349.3, U352.15
!EN18: U349.7, U353.15
!EN19: U349.6, U354.15
!EN20: U349.5, U355.15
!EN21: U420.3, U423.15
!EN22: U420.7, U424.15
!EN23: U420.6, U425.15
!EN24: U420.5, U426.15
!EN25: U491.3, U494.15
!EN26: U491.7, U495.15
!EN27: U491.6, U496.15
!EN28: U491.5, U497.15
!EN29: U562.3, U565.15
!EN30: U562.7, U566.15
!EN31: U562.6, U567.15
!EN32: U562.5, U568.15
!EN33: U633.3, U636.15
!EN34: U633.7, U637.15
!EN35: U633.6, U638.15
!EN36: U633.5, U639.15
!EN37: U704.3, U707.15
!EN38: U704.7, U708.15
!EN39: U704.6, U709.15
!EN40: U704.5, U710.15
CCLK: J1.2, U104.11, U104.13
CCLK1: J2.2, U137.11, U137.13
CCLK2: J3.2, U208.11, U208.13
CCLK3: J4.2, U279.11, U279.13
CCLK4: J5.2, U350.11, U350.13
CCLK5: J6.2, U421.11, U421.13
CCLK6: J7.2, U492.11, U492.13
CCLK7: J8.2, U563.11, U563.13
CCLK8: J9.2, U634.11, U634.13
CCLK9: J10.2, U705.11, U705.13
CS: J1.4, U106.6
CS1: J2.4, U135.6
CS2: J3.4, U206.6
CS3: J4.4, U277.6
CS4: J5.4, U348.6
CS5: J6.4, U419.6
CS6: J7.4, U490.6
CS7: J8.4, U561.6
CS8: J9.4, U632.6
CS9: J10.4, U703.6
GND: C1.2, C2.2, C3.2, C4.2, C5.2, C6.2, C7.2, C8.2, C9.2, C10.2, C11.2, J1.8, U01.3, U02.3, U03.3, U04.3, U05.3, U06.3, U07.3, U08.12, U09.3, U10.3, U11.3, U12.3, U13.3, U14.3, U15.3, U16.3, U17.3, U18.12, U19.12, U20.3, U21.3, U22.3, U23.3, U24.3, U25.3, U26.3, U27.3, U28.12, U30.3, U31.3, U32.3, U33.3, U34.3, U35.3, U36.3, U37.3, U40.3, U41.3, U42.3, U43.3, U44.3, U45.3, U46.3, U47.3, U50.3, U51.3, U52.3, U53.3, U54.3, U55.3, U56.3, U57.3, U60.3, U61.3, U62.3, U63.3, U64.3, U65.3, U66.3, U67.3, U70.3, U71.3, U72.3, U73.3, U74.3, U75.3, U76.3, U77.3, U104.8, U104.12, U104.14, U105.4, U106.2
GND1: C12.2, C13.2, C14.2, C15.2, C16.2, C17.2, C18.2, C19.2, C20.2, C21.2, C22.2, J2.8, U29.3, U38.3, U39.3, U48.3, U49.3, U58.3, U59.3, U68.3, U69.3, U78.3, U79.3, U80.3, U81.3, U82.3, U83.3, U84.3, U85.3, U86.3, U87.3, U88.3, U89.3, U90.3, U91.3, U92.3, U93.3, U94.3, U95.3, U96.3, U97.3, U98.3, U99.3, U100.3, U101.3, U102.3, U103.3, U107.3, U108.3, U109.3, U110.3, U111.3, U112.3, U113.3, U114.3, U115.3, U116.3, U117.3, U118.3, U119.3, U120.3, U121.3, U122.3, U123.3, U124.3, U125.3, U126.3, U127.3, U128.3, U129.3, U130.3, U131.3, U132.3, U133.3, U134.3, U135.2, U136.4, U137.8, U137.12, U137.14, U138.3, U139.12, U140.12, U141.12, U142.12
GND2: C23.2, C24.2, C25.2, C26.2, C27.2, C28.2, C29.2, C30.2, C31.2, C32.2, C33.2, J3.8, U143.3, U144.3, U145.3, U146.3, U147.3, U148.3, U149.3, U150.3, U151.3, U152.3, U153.3, U154.3, U155.3, U156.3, U157.3, U158.3, U159.3, U160.3, U161.3, U162.3, U163.3, U164.3, U165.3, U166.3, U167.3, U168.3, U169.3, U170.3, U171.3, U172.3, U173.3, U174.3, U175.3, U176.3, U177.3, U178.3, U179.3, U180.3, U181.3, U182.3, U183.3, U184.3, U185.3, U186.3, U187.3, U188.3, U189.3, U190.3, U191.3, U192.3, U193.3, U194.3, U195.3, U196.3, U197.3, U198.3, U199.3, U200.3, U201.3, U202.3, U203.3, U204.3, U205.3, U206.2, U207.4, U208.8, U208.12, U208.14, U209.3, U210.12, U211.12, U212.12, U213.12
GND3: C34.2, C35.2, C36.2, C37.2, C38.2, C39.2, C40.2, C41.2, C42.2, C43.2, C44.2, J4.8, U214.3, U215.3, U216.3, U217.3, U218.3, U219.3, U220.3, U221.3, U222.3, U223.3, U224.3, U225.3, U226.3, U227.3, U228.3, U229.3, U230.3, U231.3, U232.3, U233.3, U234.3, U235.3, U236.3, U237.3, U238.3, U239.3, U240.3, U241.3, U242.3, U243.3, U244.3, U245.3, U246.3, U247.3, U248.3, U249.3, U250.3, U251.3, U252.3, U253.3, U254.3, U255.3, U256.3, U257.3, U258.3, U259.3, U260.3, U261.3, U262.3, U263.3, U264.3, U265.3, U266.3, U267.3, U268.3, U269.3, U270.3, U271.3, U272.3, U273.3, U274.3, U275.3, U276.3, U277.2, U278.4, U279.8, U279.12, U279.14, U280.3, U281.12, U282.12, U283.12, U284.12
GND4: C45.2, C46.2, C47.2, C48.2, C49.2, C50.2, C51.2, C52.2, C53.2, C54.2, C55.2, J5.8, U285.3, U286.3, U287.3, U288.3, U289.3, U290.3, U291.3, U292.3, U293.3, U294.3, U295.3, U296.3, U297.3, U298.3, U299.3, U300.3, U301.3, U302.3, U303.3, U304.3, U305.3, U306.3, U307.3, U308.3, U309.3, U310.3, U311.3, U312.3, U313.3, U314.3, U315.3, U316.3, U317.3, U318.3, U319.3, U320.3, U321.3, U322.3, U323.3, U324.3, U325.3, U326.3, U327.3, U328.3, U329.3, U330.3, U331.3, U332.3, U333.3, U334.3, U335.3, U336.3, U337.3, U338.3, U339.3, U340.3, U341.3, U342.3, U343.3, U344.3, U345.3, U346.3, U347.3, U348.2, U349.4, U350.8, U350.12, U350.14, U351.3, U352.12, U353.12, U354.12, U355.12
GND5: C56.2, C57.2, C58.2, C59.2, C60.2, C61.2, C62.2, C63.2, C64.2, C65.2, C66.2, J6.8, U356.3, U357.3, U358.3, U359.3, U360.3, U361.3, U362.3, U363.3, U364.3, U365.3, U366.3, U367.3, U368.3, U369.3, U370.3, U371.3, U372.3, U373.3, U374.3, U375.3, U376.3, U377.3, U378.3, U379.3, U380.3, U381.3, U382.3, U383.3, U384.3, U385.3, U386.3, U387.3, U388.3, U389.3, U390.3, U391.3, U392.3, U393.3, U394.3, U395.3, U396.3, U397.3, U398.3, U399.3, U400.3, U401.3, U402.3, U403.3, U404.3, U405.3, U406.3, U407.3, U408.3, U409.3, U410.3, U411.3, U412.3, U413.3, U414.3, U415.3, U416.3, U417.3, U418.3, U419.2, U420.4, U421.8, U421.12, U421.14, U422.3, U423.12, U424.12, U425.12, U426.12
GND6: C67.2, C68.2, C69.2, C70.2, C71.2, C72.2, C73.2, C74.2, C75.2, C76.2, C77.2, J7.8, U427.3, U428.3, U429.3, U430.3, U431.3, U432.3, U433.3, U434.3, U435.3, U436.3, U437.3, U438.3, U439.3, U440.3, U441.3, U442.3, U443.3, U444.3, U445.3, U446.3, U447.3, U448.3, U449.3, U450.3, U451.3, U452.3, U453.3, U454.3, U455.3, U456.3, U457.3, U458.3, U459.3, U460.3, U461.3, U462.3, U463.3, U464.3, U465.3, U466.3, U467.3, U468.3, U469.3, U470.3, U471.3, U472.3, U473.3, U474.3, U475.3, U476.3, U477.3, U478.3, U479.3, U480.3, U481.3, U482.3, U483.3, U484.3, U485.3, U486.3, U487.3, U488.3, U489.3, U490.2, U491.4, U492.8, U492.12, U492.14, U493.3, U494.12, U495.12, U496.12, U497.12
GND7: C78.2, C79.2, C80.2, C81.2, C82.2, C83.2, C84.2, C85.2, C86.2, C87.2, C88.2, J8.8, U498.3, U499.3, U500.3, U501.3, U502.3, U503.3, U504.3, U505.3, U506.3, U507.3, U508.3, U509.3, U510.3, U511.3, U512.3, U513.3, U514.3, U515.3, U516.3, U517.3, U518.3, U519.3, U520.3, U521.3, U522.3, U523.3, U524.3, U525.3, U526.3, U527.3, U528.3, U529.3, U530.3, U531.3, U532.3, U533.3, U534.3, U535.3, U536.3, U537.3, U538.3, U539.3, U540.3, U541.3, U542.3, U543.3, U544.3, U545.3, U546.3, U547.3, U548.3, U549.3, U550.3, U551.3, U552.3, U553.3, U554.3, U555.3, U556.3, U557.3, U558.3, U559.3, U560.3, U561.2, U562.4, U563.8, U563.12, U563.14, U564.3, U565.12, U566.12, U567.12, U568.12
GND8: C89.2, C90.2, C91.2, C92.2, C93.2, C94.2, C95.2, C96.2, C97.2, C98.2, C99.2, J9.8, U569.3, U570.3, U571.3, U572.3, U573.3, U574.3, U575.3, U576.3, U577.3, U578.3, U579.3, U580.3, U581.3, U582.3, U583.3, U584.3, U585.3, U586.3, U587.3, U588.3, U589.3, U590.3, U591.3, U592.3, U593.3, U594.3, U595.3, U596.3, U597.3, U598.3, U599.3, U600.3, U601.3, U602.3, U603.3, U604.3, U605.3, U606.3, U607.3, U608.3, U609.3, U610.3, U611.3, U612.3, U613.3, U614.3, U615.3, U616.3, U617.3, U618.3, U619.3, U620.3, U621.3, U622.3, U623.3, U624.3, U625.3, U626.3, U627.3, U628.3, U629.3, U630.3, U631.3, U632.2, U633.4, U634.8, U634.12, U634.14, U635.3, U636.12, U637.12, U638.12, U639.12
GND9: C100.2, C101.2, C102.2, C103.2, C104.2, C105.2, C106.2, C107.2, C108.2, C109.2, C110.2, J10.8, U640.3, U641.3, U642.3, U643.3, U644.3, U645.3, U646.3, U647.3, U648.3, U649.3, U650.3, U651.3, U652.3, U653.3, U654.3, U655.3, U656.3, U657.3, U658.3, U659.3, U660.3, U661.3, U662.3, U663.3, U664.3, U665.3, U666.3, U667.3, U668.3, U669.3, U670.3, U671.3, U672.3, U673.3, U674.3, U675.3, U676.3, U677.3, U678.3, U679.3, U680.3, U681.3, U682.3, U683.3, U684.3, U685.3, U686.3, U687.3, U688.3, U689.3, U690.3, U691.3, U692.3, U693.3, U694.3, U695.3, U696.3, U697.3, U698.3, U699.3, U700.3, U701.3, U702.3, U703.2, U704.4, U705.8, U705.12, U705.14, U706.3, U707.12, U708.12, U709.12, U710.12
MISO: J1.5, U106.5
MISO1: J2.5, U135.5
MISO2: J3.5, U206.5
MISO3: J4.5, U277.5
MISO4: J5.5, U348.5
MISO5: J6.5, U419.5
MISO6: J7.5, U490.5
MISO7: J8.5, U561.5
MISO8: J9.5, U632.5
MISO9: J10.5, U703.5
unnamed: U136.1, U137.4
unnamed: U136.2, U137.5
unnamed: U207.1, U208.4
unnamed: U207.2, U208.5
unnamed: U278.1, U279.4
unnamed: U278.2, U279.5
unnamed: U104.4, U105.1
unnamed: U104.5, U105.2
unnamed: U349.1, U350.4
unnamed: U349.2, U350.5
unnamed: U420.1, U421.4
unnamed: U420.2, U421.5
unnamed: U491.1, U492.4
unnamed: U491.2, U492.5
unnamed: U562.1, U563.4
unnamed: U562.2, U563.5
unnamed: U633.1, U634.4
unnamed: U633.2, U634.5
unnamed: U704.1, U705.4
unnamed: U704.2, U705.5
OUT: J1.7, U08.1, U18.1, U19.1, U28.1, U106.3
OUT1: J2.7, U135.3, U139.1, U140.1, U141.1, U142.1
OUT2: J3.7, U206.3, U210.1, U211.1, U212.1, U213.1
OUT3: J4.7, U277.3, U281.1, U282.1, U283.1, U284.1
OUT4: J5.7, U348.3, U352.1, U353.1, U354.1, U355.1
OUT5: J6.7, U419.3, U423.1, U424.1, U425.1, U426.1
OUT6: J7.7, U490.3, U494.1, U495.1, U496.1, U497.1
OUT7: J8.7, U561.3, U565.1, U566.1, U567.1, U568.1
OUT8: J9.7, U632.3, U636.1, U637.1, U638.1, U639.1
OUT9: J10.7, U703.3, U707.1, U708.1, U709.1, U710.1
S0: U08.10, U18.10, U19.10, U28.10, U104.15
S1: U08.11, U18.11, U19.11, U28.11, U104.1
S2: U08.14, U18.14, U19.14, U28.14, U104.2
S3: U08.13, U18.13, U19.13, U28.13, U104.3
S4: U137.15, U139.10, U140.10, U141.10, U142.10
S5: U137.1, U139.11, U140.11, U141.11, U142.11
S6: U137.2, U139.14, U140.14, U141.14, U142.14
S7: U137.3, U139.13, U140.13, U141.13, U142.13
S8: U208.15, U210.10, U211.10, U212.10, U213.10
S9: U208.1, U210.11, U211.11, U212.11, U213.11
S10: U208.2, U210.14, U211.14, U212.14, U213.14
S11: U208.3, U210.13, U211.13, U212.13, U213.13
S12: U279.15, U281.10, U282.10, U283.10, U284.10
S13: U279.1, U281.11, U282.11, U283.11, U284.11
S14: U279.2, U281.14, U282.14, U283.14, U284.14
S15: U279.3, U281.13, U282.13, U283.13, U284.13
S16: U350.15, U352.10, U353.10, U354.10, U355.10
S17: U350.1, U352.11, U353.11, U354.11, U355.11
S18: U350.2, U352.14, U353.14, U354.14, U355.14
S19: U350.3, U352.13, U353.13, U354.13, U355.13
S20: U421.15, U423.10, U424.10, U425.10, U426.10
S21: U421.1, U423.11, U424.11, U425.11, U426.11
S22: U421.2, U423.14, U424.14, U425.14, U426.14
S23: U421.3, U423.13, U424.13, U425.13, U426.13
S24: U492.15, U494.10, U495.10, U496.10, U497.10
S25: U492.1, U494.11, U495.11, U496.11, U497.11
S26: U492.2, U494.14, U495.14, U496.14, U497.14
S27: U492.3, U494.13, U495.13, U496.13, U497.13
S28: U563.15, U565.10, U566.10, U567.10, U568.10
S29: U563.1, U565.11, U566.11, U567.11, U568.11
S30: U563.2, U565.14, U566.14, U567.14, U568.14
S31: U563.3, U565.13, U566.13, U567.13, U568.13
S32: U634.15, U636.10, U637.10, U638.10, U639.10
S33: U634.1, U636.11, U637.11, U638.11, U639.11
S34: U634.2, U636.14, U637.14, U638.14, U639.14
S35: U634.3, U636.13, U637.13, U638.13, U639.13
S36: U705.15, U707.10, U708.10, U709.10, U710.10
S37: U705.1, U707.11, U708.11, U709.11, U710.11
S38: U705.2, U707.14, U708.14, U709.14, U710.14
S39: U705.3, U707.13, U708.13, U709.13, U710.13
SCLK: J1.6, U106.4
SCLK1: J2.6, U135.4
SCLK2: J3.6, U206.4
SCLK3: J4.6, U277.4
SCLK4: J5.6, U348.4
SCLK5: J6.6, U419.4
SCLK6: J7.6, U490.4
SCLK7: J8.6, U561.4
SCLK8: J9.6, U632.4
SCLK9: J10.6, U703.4

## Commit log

2024-07-11 Initial commit
    -Pulled files from spx repo
    -Updated silk
2024-07-11 Silk Update
    Removed name and date from old design
2024-07-12 Update
    -Changes silk to vector
    -Added order instructions
    -Updated Design By
    -OSH and SPARKFUN added to sch and board as part
2024-07-19 Add v10 production files
2024-08-08 Initial Push GitHub Pages
2024-08-22 Add Hardware Overview, Hardware Hookup, and Photos
2024-08-23 Add hookup table, update code to default, include notes
2024-10-28 Add cookies and fix minor spelling error
2026-06-03 Deployed 68fdbfb with MkDocs version: 1.6.1
